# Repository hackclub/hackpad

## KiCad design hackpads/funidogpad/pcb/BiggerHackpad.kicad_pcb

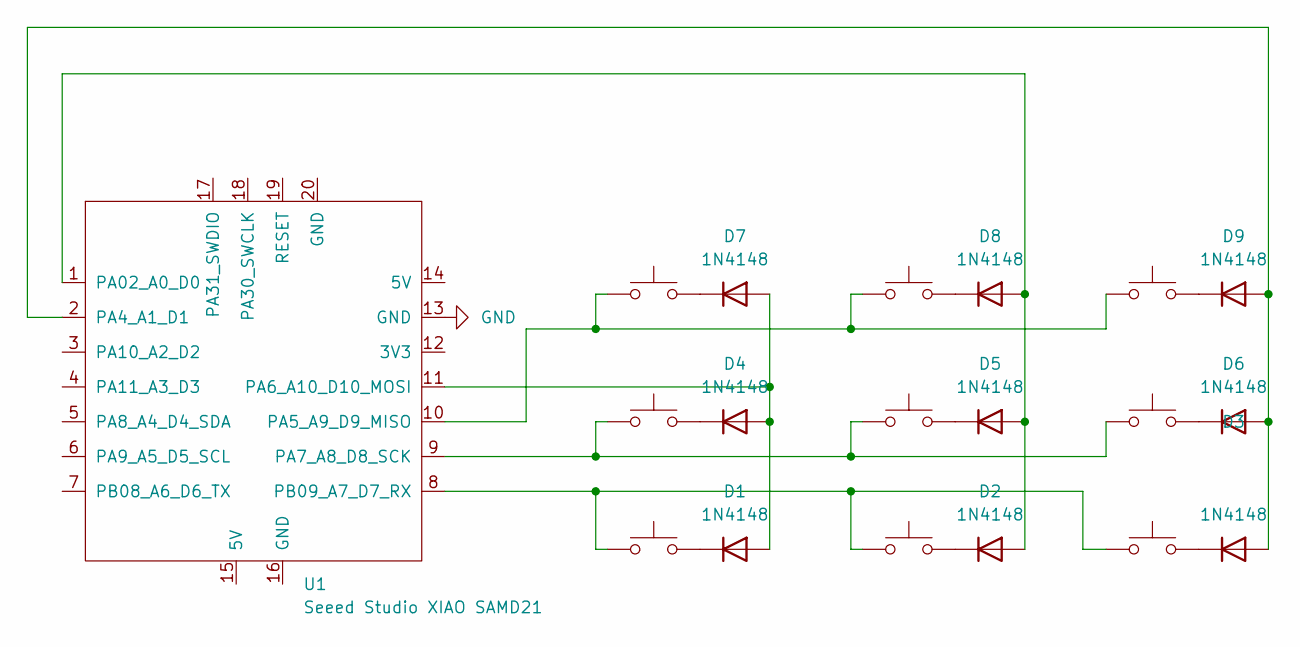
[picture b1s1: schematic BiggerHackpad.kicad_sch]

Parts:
D1, D2, D3, D4, D5, D6, D7, D8, D9: 1N4148; D_DO-35_SOD27_P7.62mm_Horizontal
SW1, SW2, SW3, SW4, SW5, SW6, SW7, SW8, SW9: SW_Push; SW_Cherry_MX_1.00u_PCB
U1: Seeed Studio XIAO SAMD21; XIAO-SAMD21-RP2040-14P-2.54-21X17.8MM (Seeeduino XIAO)

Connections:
GND: U1.13 (GND)
unnamed: D1.2 (A), D4.2 (A), D7.2 (A), U1.11 (PA6_A10_D10_MOSI)
unnamed: D1.1 (K), SW1.2
unnamed: D2.2 (A), D5.2 (A), D8.2 (A), U1.1 (PA02_A0_D0)
unnamed: D2.1 (K), SW2.2
unnamed: D3.2 (A), D6.2 (A), D9.2 (A), U1.2 (PA4_A1_D1)
unnamed: D3.1 (K), SW3.2
unnamed: D4.1 (K), SW4.2
unnamed: D5.1 (K), SW5.2
unnamed: D6.1 (K), SW6.2
unnamed: D7.1 (K), SW7.2
unnamed: D8.1 (K), SW8.2
unnamed: D9.1 (K), SW9.2
unnamed: SW7.1, SW8.1, SW9.1, U1.10 (PA5_A9_D9_MISO)
unnamed: SW4.1, SW5.1, SW6.1, U1.9 (PA7_A8_D8_SCK)
unnamed: SW1.1, SW2.1, SW3.1, U1.8 (PB09_A7_D7_RX)

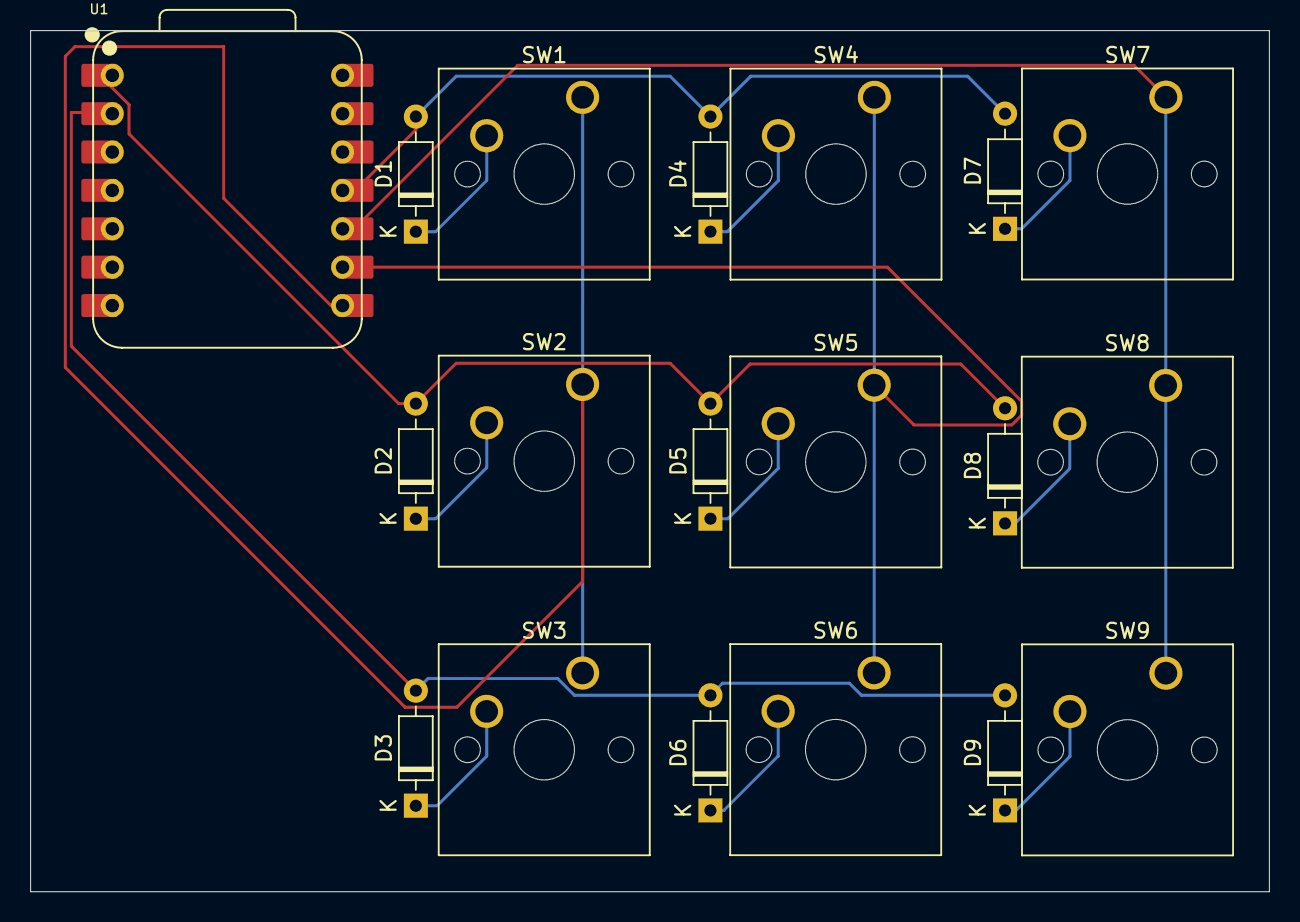
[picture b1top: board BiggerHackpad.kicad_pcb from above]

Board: 2 copper layers, 82.0 x 57.0 mm, 19 parts (0 on the bottom side), 15 nets.

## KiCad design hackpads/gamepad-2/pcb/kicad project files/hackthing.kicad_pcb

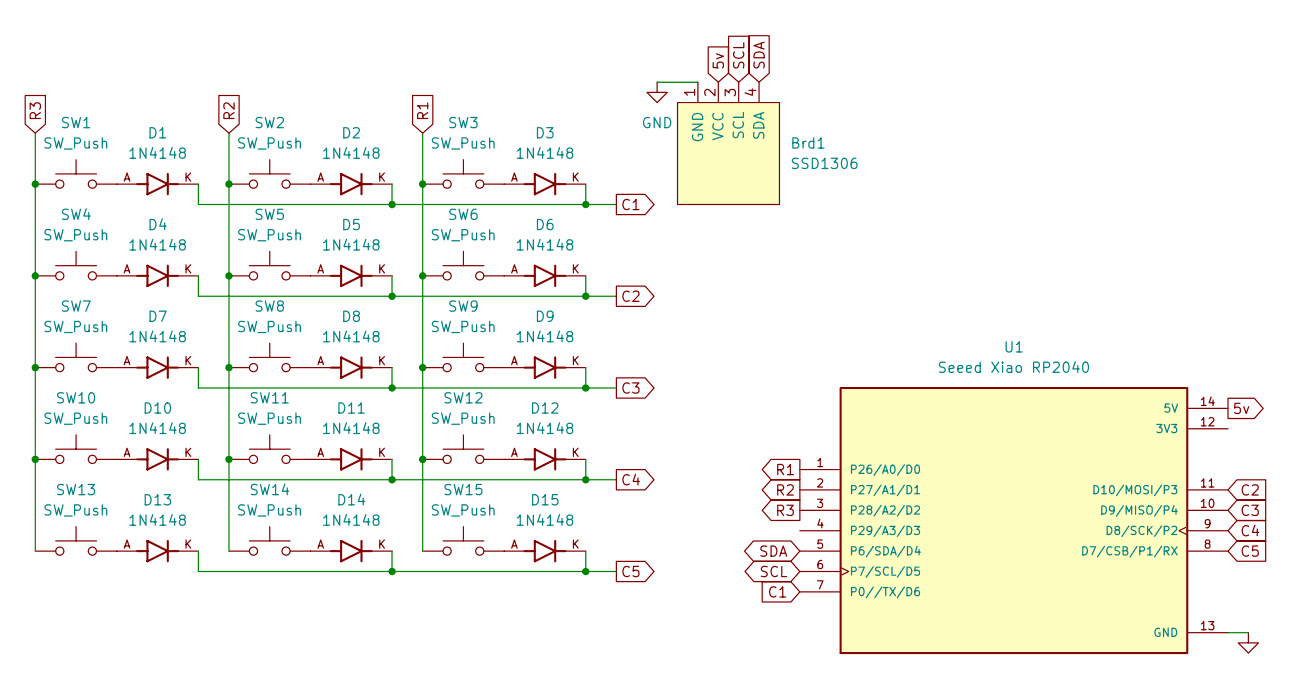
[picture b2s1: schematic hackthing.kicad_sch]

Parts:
Brd1: SSD1306; 128x64OLED
D1, D2, D3, D4, D5, D6, D7, D8, D9, D10, D11, D12, D13, D14, D15: 1N4148; DIOAD753W49L380D172B; PARTREV 5
SW1, SW2, SW3, SW4, SW5, SW6, SW7, SW8, SW9, SW10, SW11, SW12, SW13, SW14, SW15: SW_Push; MX-Solderable-1U
U1: Seeed Xiao RP2040; XIAO-Generic-Thruhole-14P-2.54-21X17.8MM; PARTREV 1.3

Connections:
5v: Brd1.2 (VCC), U1.14 (5V)
C1: D1.K, D2.K, D3.K, U1.7 (P0//TX/D6)
C2: D4.K, D5.K, D6.K, U1.11 (D10/MOSI/P3)
C3: D7.K, D8.K, D9.K, U1.10 (D9/MISO/P4)
C4: D10.K, D11.K, D12.K, U1.9 (D8/SCK/P2)
C5: D13.K, D14.K, D15.K, U1.8 (D7/CSB/P1/RX)
GND: Brd1.1 (GND), U1.13 (GND)
unnamed: D1.A, SW1.2
unnamed: D2.A, SW2.2
unnamed: D3.A, SW3.2
unnamed: D4.A, SW4.2
unnamed: D5.A, SW5.2
unnamed: D6.A, SW6.2
unnamed: D7.A, SW7.2
unnamed: D8.A, SW8.2
unnamed: D9.A, SW9.2
unnamed: D10.A, SW10.2
unnamed: D11.A, SW11.2
unnamed: D12.A, SW12.2
unnamed: D13.A, SW13.2
unnamed: D14.A, SW14.2
unnamed: D15.A, SW15.2
R1: SW3.1, SW6.1, SW9.1, SW12.1, SW15.1, U1.1 (P26/A0/D0)
R2: SW2.1, SW5.1, SW8.1, SW11.1, SW14.1, U1.2 (P27/A1/D1)
R3: SW1.1, SW4.1, SW7.1, SW10.1, SW13.1, U1.3 (P28/A2/D2)
SCL: Brd1.3 (SCL), U1.6 (P7/SCL/D5)
SDA: Brd1.4 (SDA), U1.5 (P6/SDA/D4)

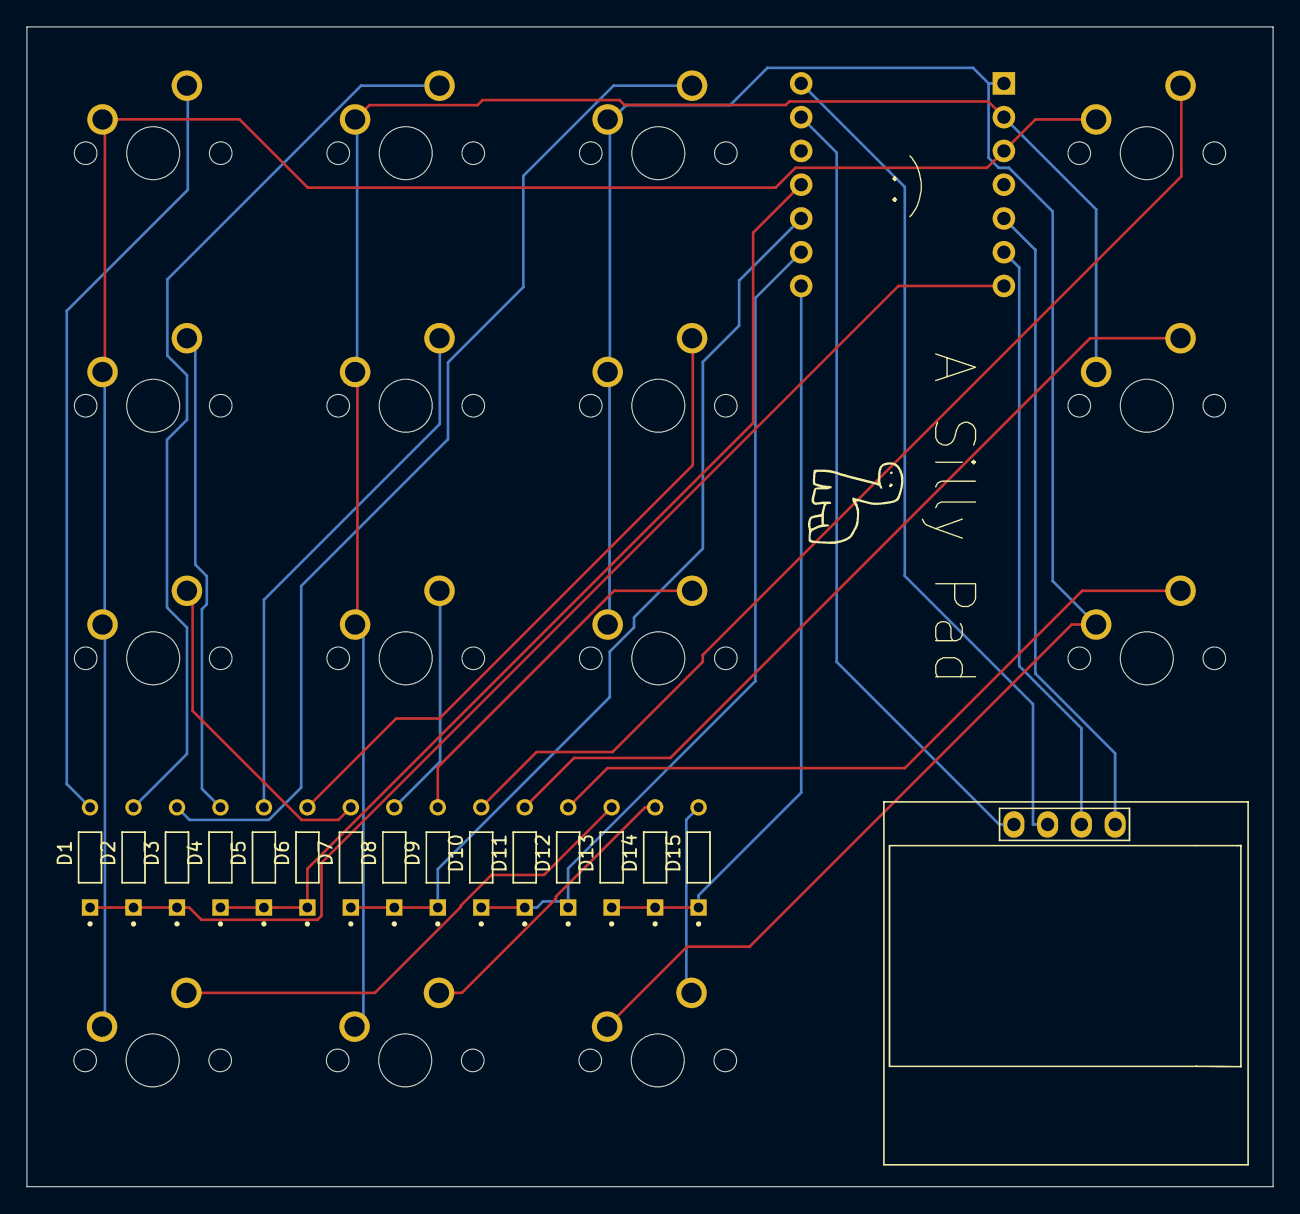
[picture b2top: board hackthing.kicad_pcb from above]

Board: 2 copper layers, 93.8 x 87.2 mm, 33 parts (1 on the bottom side), 27 nets.

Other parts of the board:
dino: LOGO

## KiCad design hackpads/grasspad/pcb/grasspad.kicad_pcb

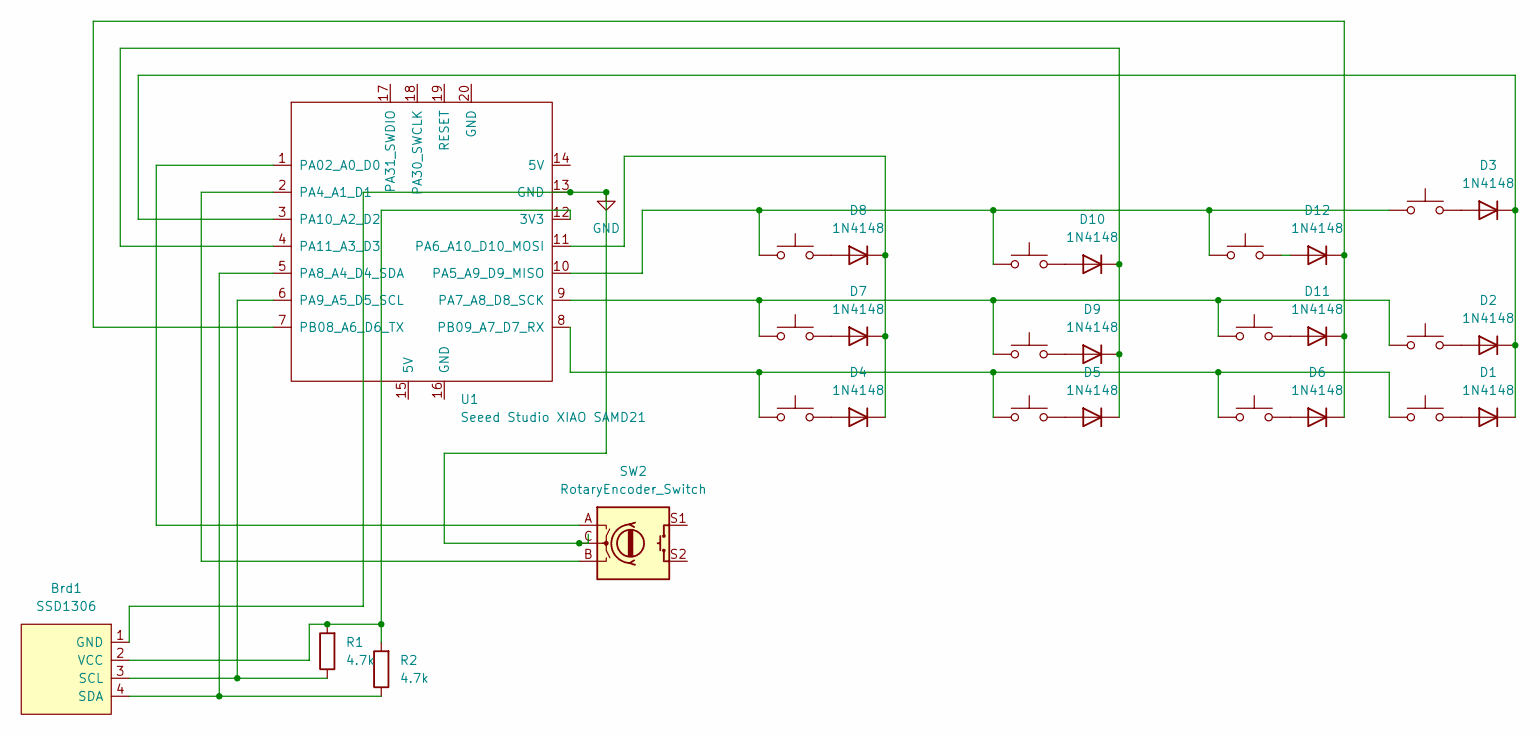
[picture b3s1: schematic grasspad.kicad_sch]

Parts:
Brd1: SSD1306; Adafruit_SSD1306
D1, D2, D3, D4, D5, D6, D7, D8, D9, D10, D11, D12: 1N4148; D_DO-35_SOD27_P7.62mm_Horizontal
R1, R2: 4.7k
SW1, SW3, SW4, SW5, SW6, SW7, SW8, SW9, SW10, SW11, SW12, SW13: SW_Push; SW_Cherry_MX_1.00u_PCB
SW2: RotaryEncoder_Switch; RotaryEncoder_Alps_EC11E-Switch_Vertical_H20mm
U1: Seeed Studio XIAO SAMD21; XIAO-Generic-Thruhole-14P-2.54-21X17.8MM

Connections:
GND: Brd1.1 (GND), SW2.C, U1.13 (GND)
unnamed: Brd1.3 (SCL), R1.1, U1.6 (PA9_A5_D5_SCL)
unnamed: Brd1.4 (SDA), R2.1, U1.5 (PA8_A4_D4_SDA)
unnamed: Brd1.2 (VCC), R1.2, R2.2, U1.12 (3V3)
unnamed: D1.2 (A), SW5.2
unnamed: D1.1 (K), D2.1 (K), D3.1 (K), U1.3 (PA10_A2_D2)
unnamed: D2.2 (A), SW1.2
unnamed: D3.2 (A), SW3.2
unnamed: D4.2 (A), SW4.2
unnamed: D4.1 (K), D7.1 (K), D8.1 (K), U1.11 (PA6_A10_D10_MOSI)
unnamed: D5.2 (A), SW6.2
unnamed: D6.2 (A), SW7.2
unnamed: D7.2 (A), SW8.2
unnamed: D8.2 (A), SW9.2
unnamed: D9.2 (A), SW10.2
unnamed: D10.2 (A), SW11.2
unnamed: D5.1 (K), D9.1 (K), D10.1 (K), U1.4 (PA11_A3_D3)
unnamed: D11.2 (A), SW12.2
unnamed: D6.1 (K), D11.1 (K), D12.1 (K), U1.7 (PB08_A6_D6_TX)
unnamed: D12.2 (A), SW13.2
unnamed: SW2.A, U1.1 (PA02_A0_D0)
unnamed: SW2.B, U1.2 (PA4_A1_D1)
unnamed: SW3.1, SW9.1, SW11.1, SW13.1, U1.10 (PA5_A9_D9_MISO)
unnamed: SW1.1, SW8.1, SW10.1, SW12.1, U1.9 (PA7_A8_D8_SCK)
unnamed: SW4.1, SW5.1, SW6.1, SW7.1, U1.8 (PB09_A7_D7_RX)

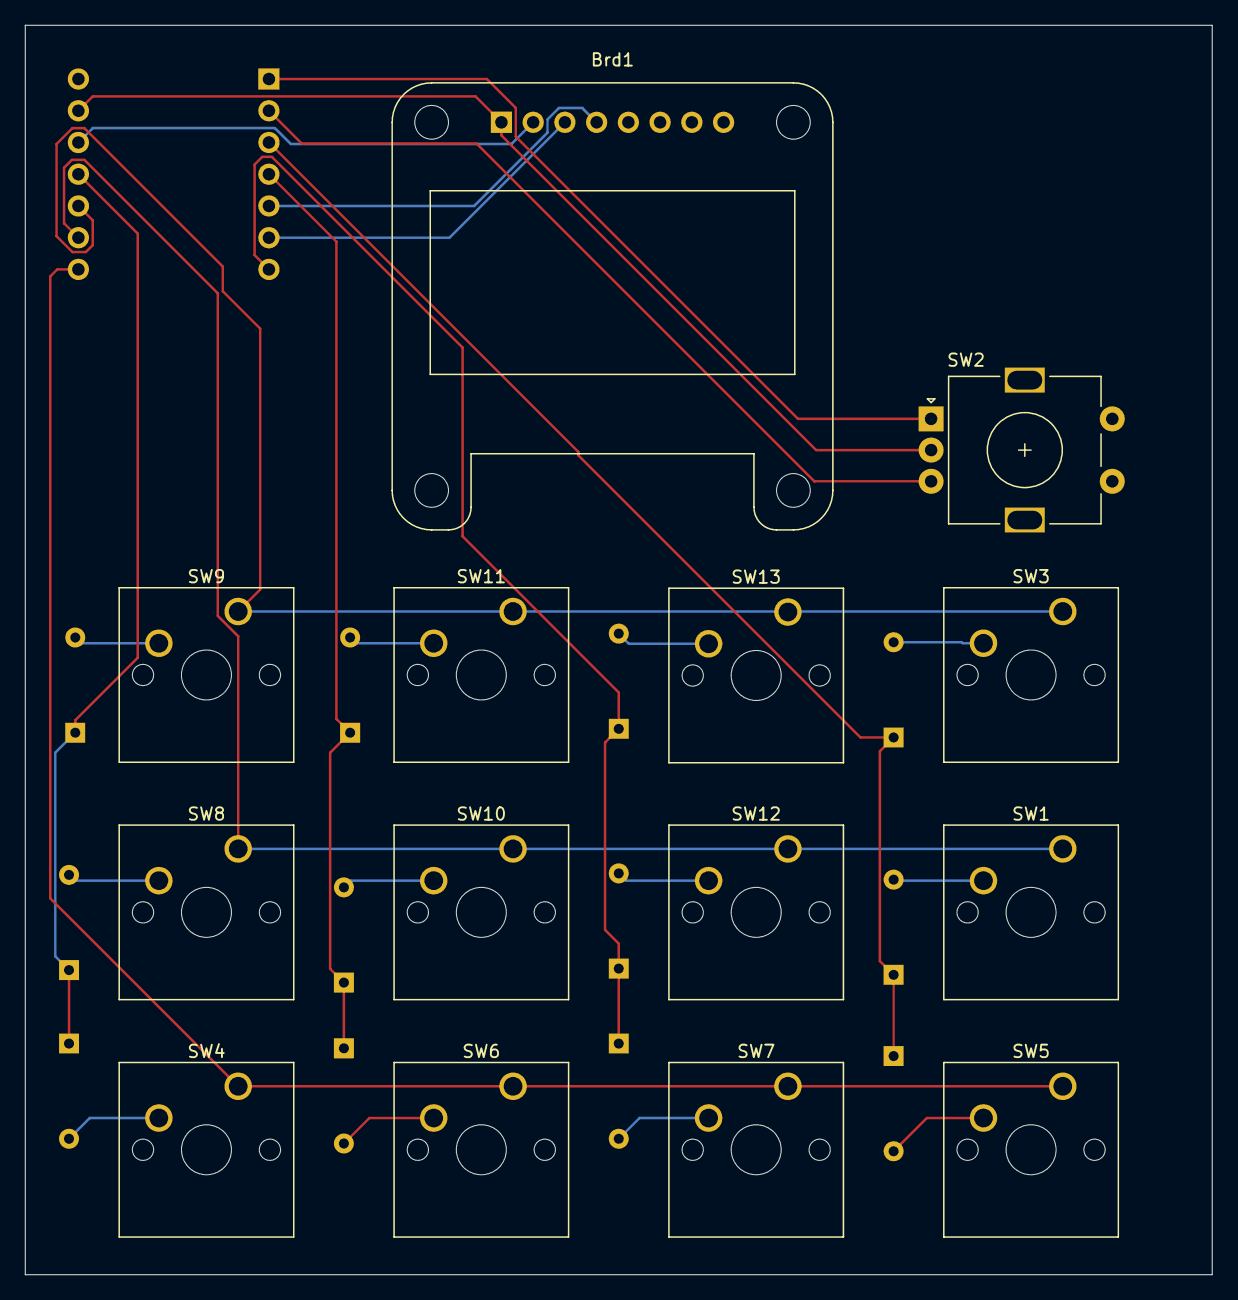
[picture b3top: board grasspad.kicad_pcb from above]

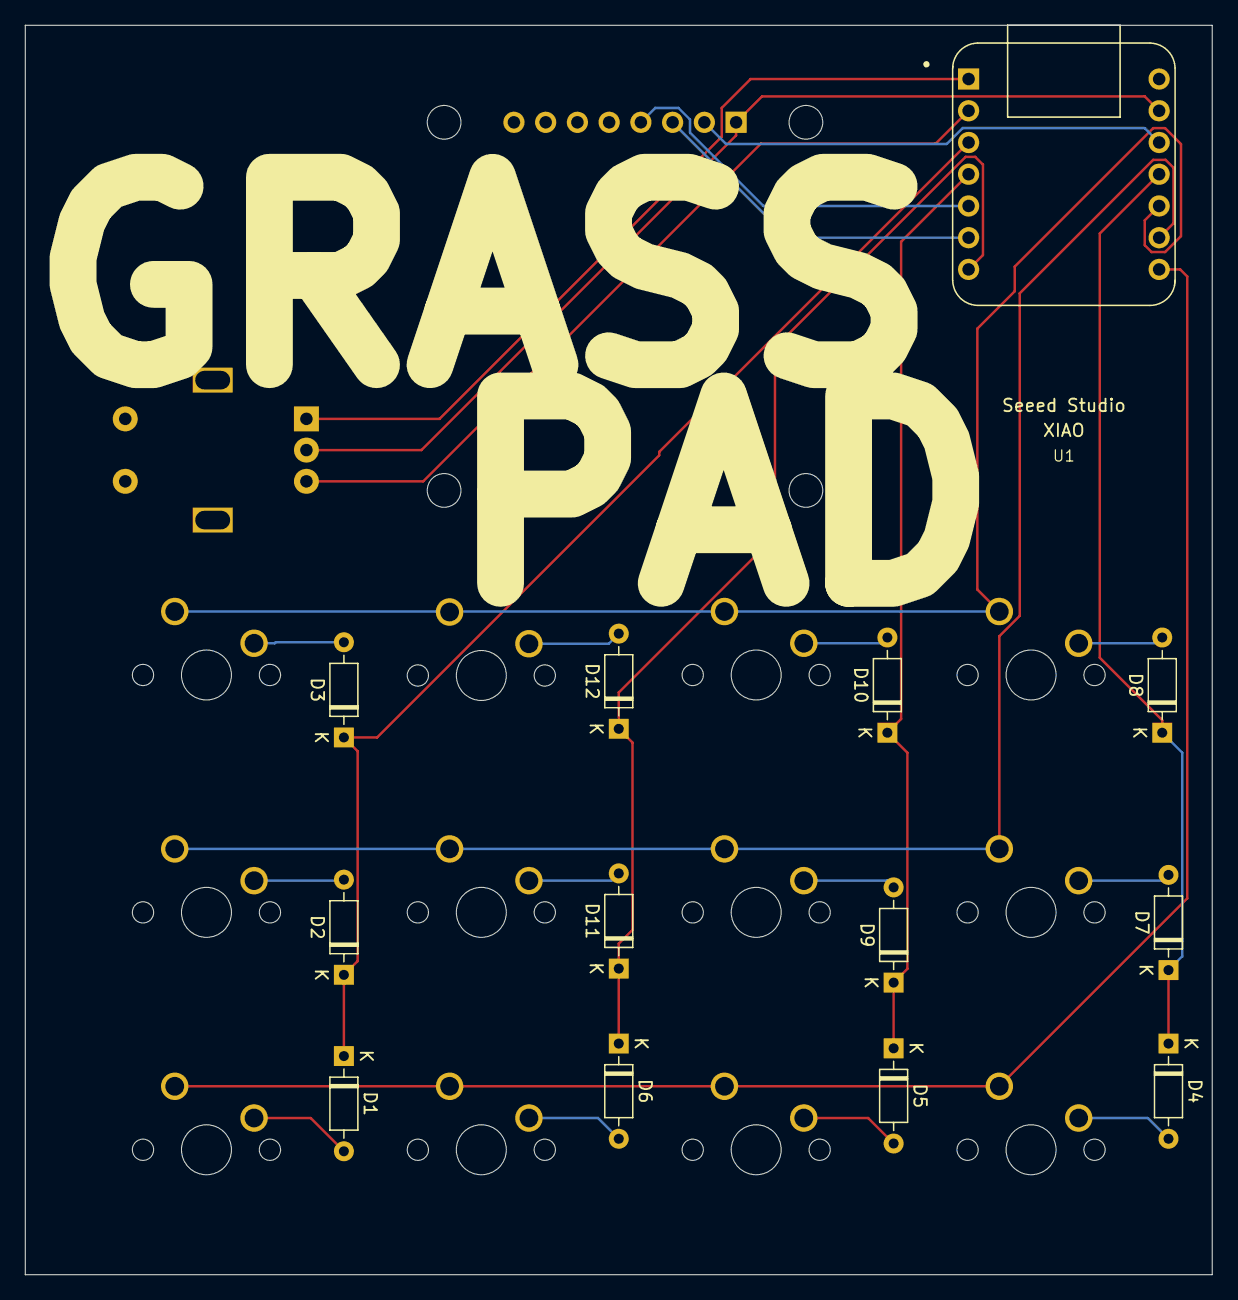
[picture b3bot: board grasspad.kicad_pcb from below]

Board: 2 copper layers, 95.0 x 100.0 mm, 27 parts (13 on the bottom side), 25 nets.

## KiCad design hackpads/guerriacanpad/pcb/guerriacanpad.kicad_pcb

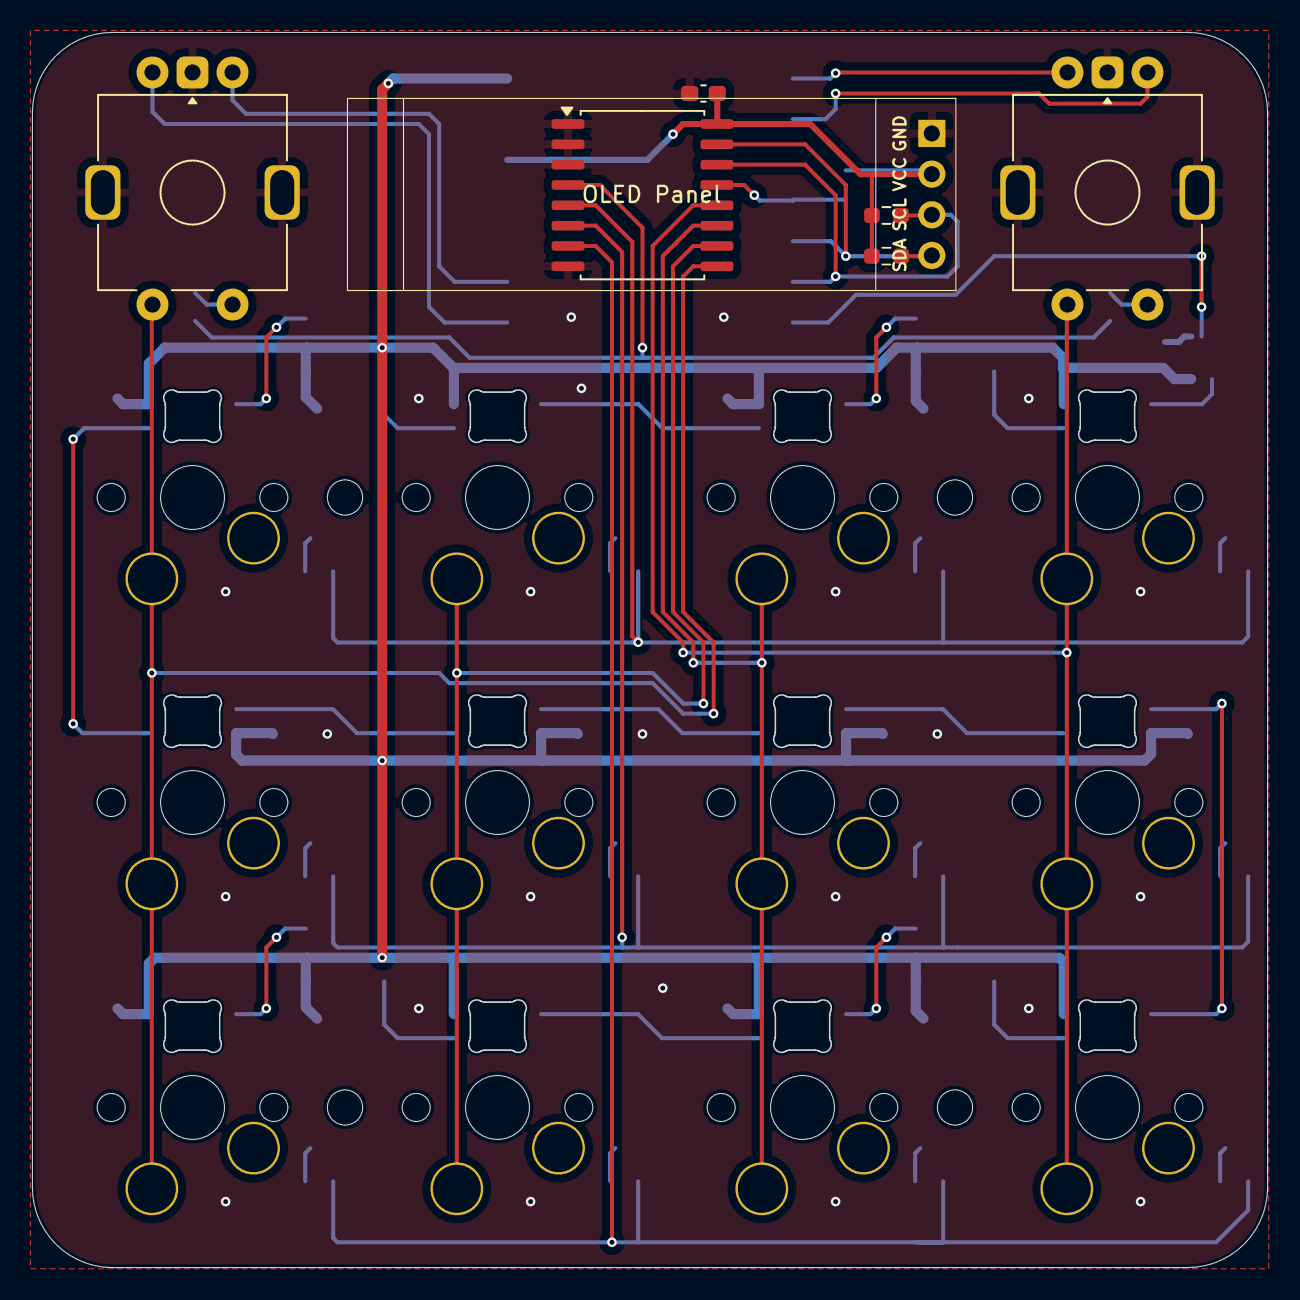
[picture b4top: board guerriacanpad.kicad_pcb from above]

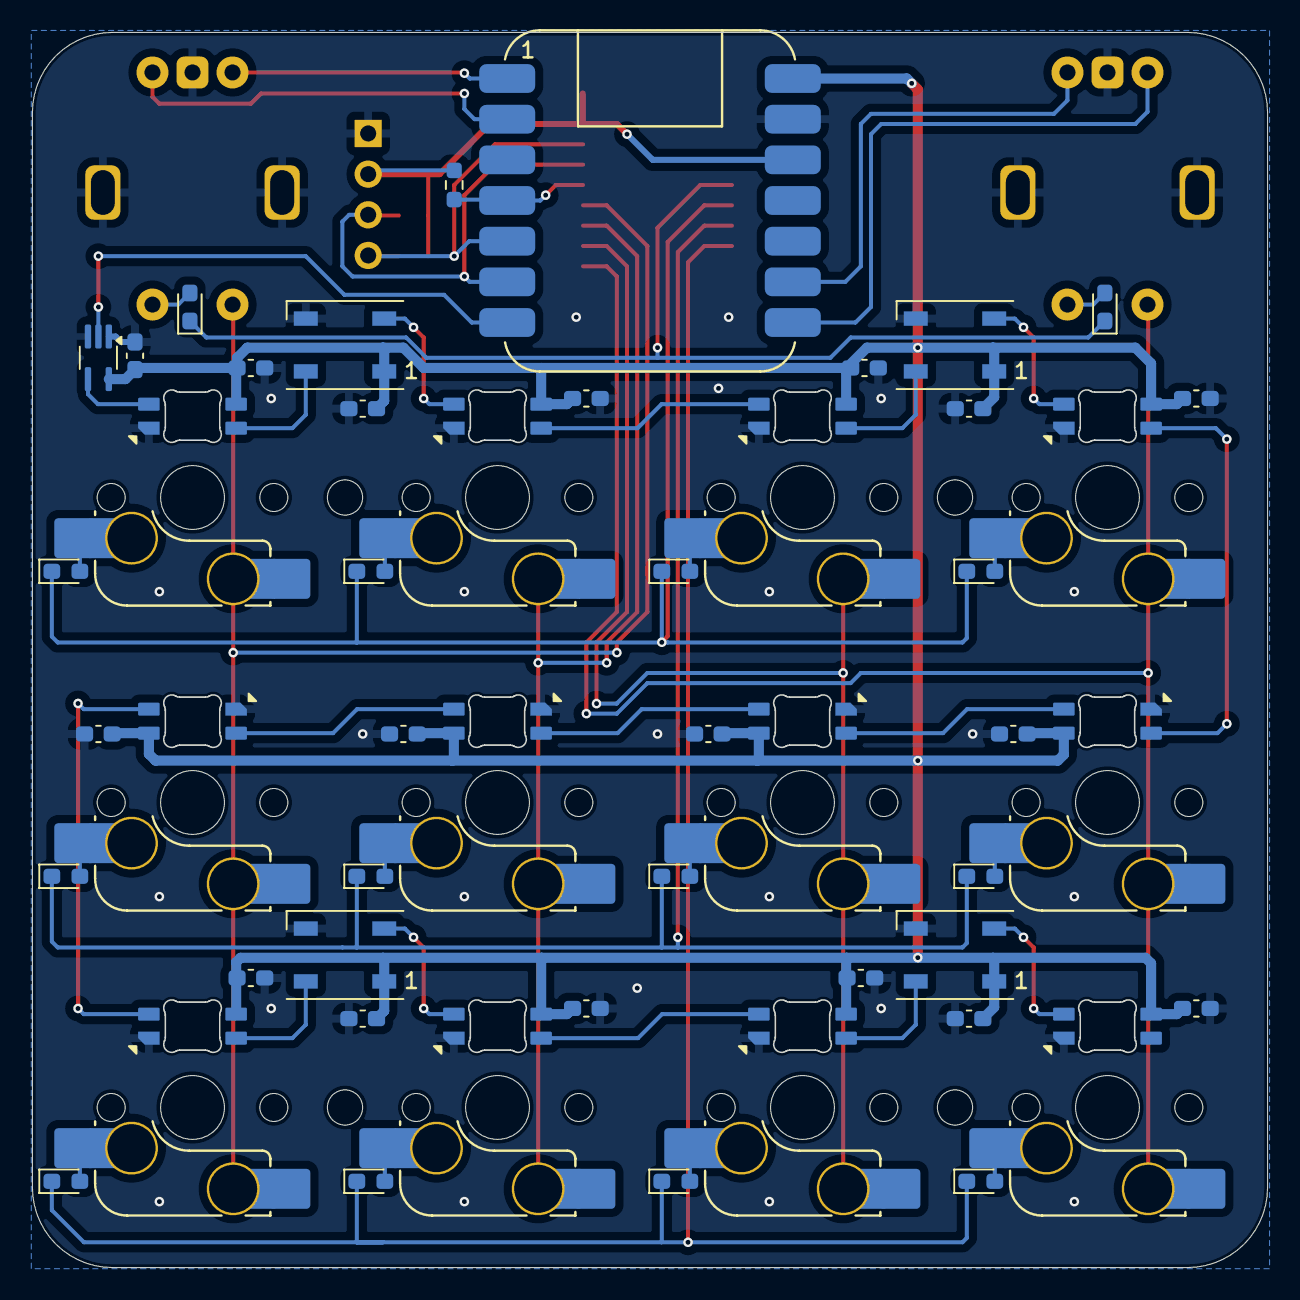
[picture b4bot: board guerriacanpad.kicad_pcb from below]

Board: 2 copper layers, 77.2 x 77.2 mm, 73 parts (62 on the bottom side), 49 nets.

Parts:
C1, C2, C3, C4, C5, C6, C7, C8, C9, C10, C11, C12, C13, C14, C15, C16, C17, C18: 100nF; C_0603_1608Metric_Pad1.08x0.95mm_HandSolder
D1, D2, D3, D4, D5, D6, D7, D8, D9, D10, D11, D12, D13, D14: D_Small; D_0603_1608Metric_Pad1.05x0.95mm_HandSolder
DS1: SSD1306_OLED_I2C; SSD1306-0.91-OLED-4pin-128x32
H1, H2, H3, H4: MountingHole; MountingHole_2.2mm_M2
LED1, LED2, LED3, LED4, LED9, LED10, LED11, LED12: SK6812MINI-E; LED_MX_6028R-ROT
LED5, LED6, LED7, LED8: SK6812MINI-E; LED_MX_6028R
LED13, LED14, LED15, LED16: WS2812B; LED_WS2812B_PLCC4_5.0x5.0mm_P3.2mm
MX1, MX2, MX3, MX4, MX5, MX6, MX7, MX8, MX9, MX10, MX11, MX12: MX_SW_HS; SW_MX_HS_CPG151101S11_1u
R1, R2: 4k7; R_0603_1608Metric_Pad0.98x0.95mm_HandSolder
R3: 10k; R_0603_1608Metric_Pad0.98x0.95mm_HandSolder
SW1, SW2: RotaryEncoder_Switch_MP; ROT_Alps_EC11E-Switch
U1: Seeeduino Xiao rp2040; Xiao_rp2040_AC_Reflow
U2: PCF8574; SOIC-16W_7.5x10.3mm_P1.27mm
U3: 74AHC1G125; SOT-353_SC-70-5_Handsoldering

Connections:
+3.3V: C17.2, DS1.2 (VCC), R1.2, R2.1, R3.1, U1.10 (3V3), U2.16 (VDD)
+5V: C1.1, C2.1, C3.1, C4.1, C5.1, C6.1, C7.1, C8.1, C9.1, C10.1, C11.1, C12.1, C13.1, C14.1, C15.1, C16.1, C18.2, LED1.1 (VDD), LED2.1 (VDD), LED3.1 (VDD), LED4.1 (VDD), LED5.1 (VDD), LED6.1 (VDD), LED7.1 (VDD), LED8.1 (VDD), LED9.1 (VDD), LED10.1 (VDD), LED11.1 (VDD), LED12.1 (VDD), LED13.1 (VDD), LED14.1 (VDD), LED15.1 (VDD), LED16.1 (VDD), U1.8 (5V), U3.5 (VCC)
COLUMN1: MX1.2, MX5.2, MX9.2, SW1.S1, U2.9 (P4)
COLUMN2: MX2.2, MX6.2, MX10.2, U2.10 (P5)
COLUMN3: MX3.2, MX7.2, MX11.2, U2.11 (P6)
COLUMN4: MX4.2, MX8.2, MX12.2, SW2.S1, U2.12 (P7)
D_LEDS_3V3: U1.7 (P0), U3.2
D_LEDS_5V: LED4.3 (DIN), U3.4
GND: C1.2, C2.2, C3.2, C4.2, C5.2, C6.2, C7.2, C8.2, C9.2, C10.2, C11.2, C12.2, C13.2, C14.2, C15.2, C16.2, C17.1, C18.1, DS1.1 (GND), LED1.4 (VSS), LED2.4 (VSS), LED3.4 (VSS), LED4.4 (VSS), LED5.4 (VSS), LED6.4 (VSS), LED7.4 (VSS), LED8.4 (VSS), LED9.4 (VSS), LED10.4 (VSS), LED11.4 (VSS), LED12.4 (VSS), LED13.3 (VSS), LED14.3 (VSS), LED15.3 (VSS), LED16.3 (VSS), SW1.C, SW1.MP, SW2.C, SW2.MP, U1.9 (GND), U2.1 (A0), U2.2 (A1), U2.3 (A2), U2.8 (VSS), U3.1, U3.3 (GND)
INT: R3.2, U1.4 (P29), U2.13 (~INT)
unnamed: D1.2 (A), MX1.1
unnamed: D2.2 (A), MX2.1
unnamed: D3.2 (A), MX3.1
unnamed: D4.2 (A), MX4.1
unnamed: D5.2 (A), MX5.1
unnamed: D6.2 (A), MX6.1
unnamed: D7.2 (A), MX7.1
unnamed: D8.2 (A), MX8.1
unnamed: D9.2 (A), MX9.1
unnamed: D10.2 (A), MX10.1
unnamed: D11.2 (A), MX11.1
unnamed: D12.2 (A), MX12.1
unnamed: D13.2 (A), SW1.S2
unnamed: D14.2 (A), SW2.S2
unnamed: LED1.3 (DIN), LED13.2 (DOUT)
unnamed: LED1.2 (DOUT), LED5.3 (DIN)
unnamed: LED2.3 (DIN), LED3.2 (DOUT)
unnamed: LED5.2 (DOUT), LED6.3 (DIN)
unnamed: LED6.2 (DOUT), LED7.3 (DIN)
unnamed: LED7.2 (DOUT), LED8.3 (DIN)
unnamed: LED10.3 (DIN), LED11.2 (DOUT)
unnamed: LED10.2 (DOUT), LED15.4 (DIN)
unnamed: LED11.3 (DIN), LED16.2 (DOUT)
unnamed: LED8.2 (DOUT), LED12.3 (DIN)
unnamed: LED12.2 (DOUT), LED16.4 (DIN)
unnamed: LED2.2 (DOUT), LED13.4 (DIN)
unnamed: LED4.2 (DOUT), LED14.4 (DIN)
unnamed: LED3.3 (DIN), LED14.2 (DOUT)
unnamed: LED9.3 (DIN), LED15.2 (DOUT)
ROT1A: SW1.A, U1.13 (P2)
ROT1B: SW1.B, U1.14 (P1)
ROT2A: SW2.A, U1.2 (P27)
ROT2B: SW2.B, U1.1 (P26)
ROW1: D13.1 (K), D14.1 (K), U2.4 (P0)
ROW2: D1.1 (K), D2.1 (K), D3.1 (K), D4.1 (K), U2.5 (P1)
ROW3: D5.1 (K), D6.1 (K), D7.1 (K), D8.1 (K), U2.6 (P2)
ROW4: D9.1 (K), D10.1 (K), D11.1 (K), D12.1 (K), U2.7 (P3)
SCL: DS1.3 (SCL), R2.2, U1.6 (P7), U2.14 (SCL)
SDA: DS1.4 (SDA), R1.1, U1.5 (P6), U2.15 (SDA)

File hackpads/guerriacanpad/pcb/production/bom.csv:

Designator,Footprint,Quantity,Value,LCSC Part #
"D1, D10, D11, D12, D17, D18, D2, D3, D4, D5, D6, D7, D8, D9",0603,14,D_Small,
"D13, D14, D15, D16",LED_WS2812B_PLCC4_5.0x5.0mm_P3.2mm,4,WS2812B,
DS1,SSD1306-0.91-OLED-4pin-128x32,1,SSD1306_OLED_I2C,
"LED1, LED10, LED11, LED12, LED2, LED3, LED4, LED9",LED_MX_6028R-ROT,8,SK6812MINI-E,
"LED5, LED6, LED7, LED8",LED_MX_6028R,4,SK6812MINI-E,
"MX1, MX10, MX11, MX12, MX2, MX3, MX4, MX5, MX6, MX7, MX8, MX9",SW_MX_HS_CPG151101S11_1u,12,MX_SW_HS,
"SW1, SW2",ROT_Alps_EC11E-Switch,2,RotaryEncoder_Switch_MP,
U2,SOIC-16W_7.5x10.3mm_P1.27mm,1,PCF8574,
U3,SOT-353_SC-70-5_Handsoldering,1,74AHC1G125,

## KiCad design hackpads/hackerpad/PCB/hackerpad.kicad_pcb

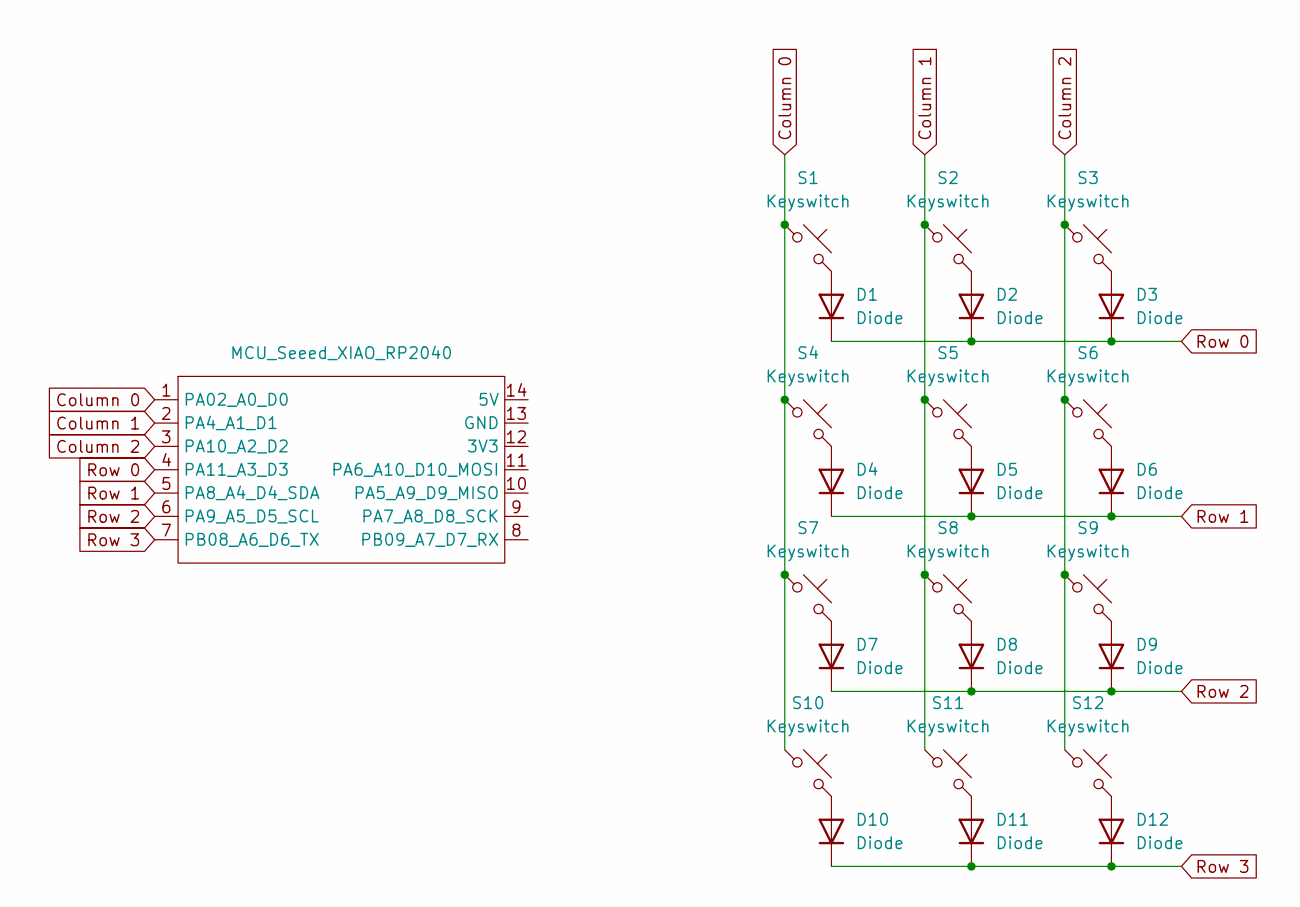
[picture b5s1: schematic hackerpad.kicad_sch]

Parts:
D1, D2, D3, D4, D5, D6, D7, D8, D9, D10, D11, D12: Diode; Diode_DO-35
S1, S2, S3, S4, S5, S6, S7, S8, S9, S10, S11, S12: Keyswitch; MX_PCB_1.00u
U1: MCU_Seeed_XIAO_RP2040; Seeed_XIAO_RP2040

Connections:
Column 0: S1.1, S4.1, S7.1, S10.1, U1.1 (PA02_A0_D0)
Column 1: S2.1, S5.1, S8.1, S11.1, U1.2 (PA4_A1_D1)
Column 2: S3.1, S6.1, S9.1, S12.1, U1.3 (PA10_A2_D2)
unnamed: D1.2 (A), S1.2
unnamed: D2.2 (A), S2.2
unnamed: D3.2 (A), S3.2
unnamed: D4.2 (A), S4.2
unnamed: D5.2 (A), S5.2
unnamed: D6.2 (A), S6.2
unnamed: D7.2 (A), S7.2
unnamed: D8.2 (A), S8.2
unnamed: D9.2 (A), S9.2
unnamed: D10.2 (A), S10.2
unnamed: D11.2 (A), S11.2
unnamed: D12.2 (A), S12.2
Row 0: D1.1 (K), D2.1 (K), D3.1 (K), U1.4 (PA11_A3_D3)
Row 1: D4.1 (K), D5.1 (K), D6.1 (K), U1.5 (PA8_A4_D4_SDA)
Row 2: D7.1 (K), D8.1 (K), D9.1 (K), U1.6 (PA9_A5_D5_SCL)
Row 3: D10.1 (K), D11.1 (K), D12.1 (K), U1.7 (PB08_A6_D6_TX)

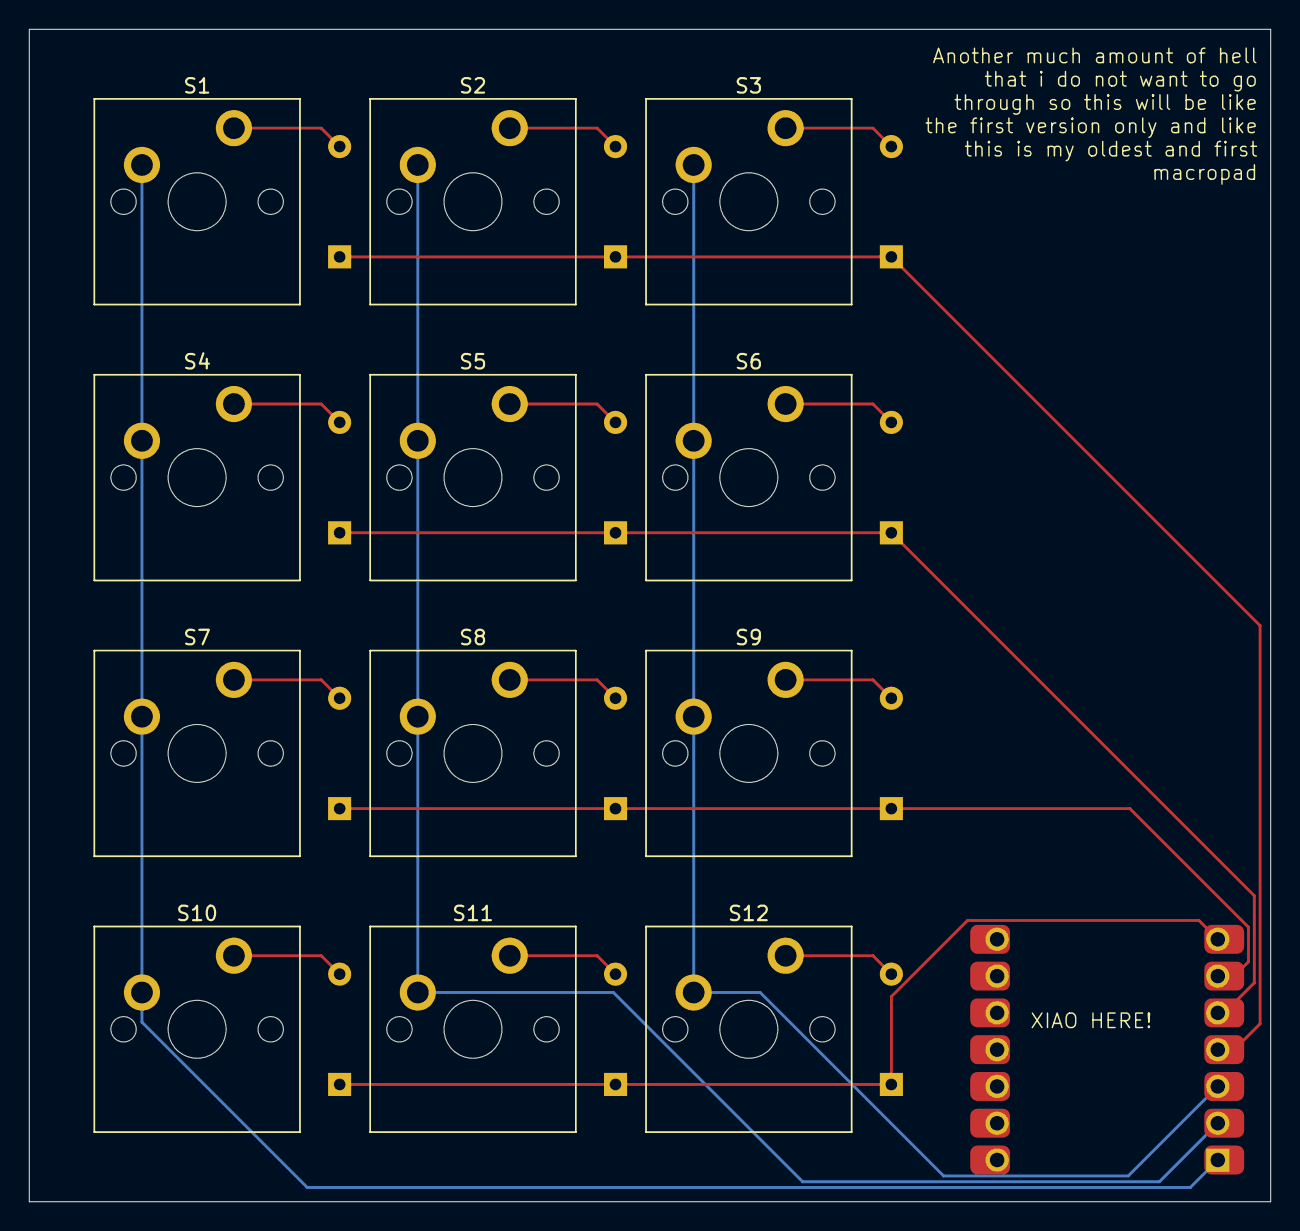
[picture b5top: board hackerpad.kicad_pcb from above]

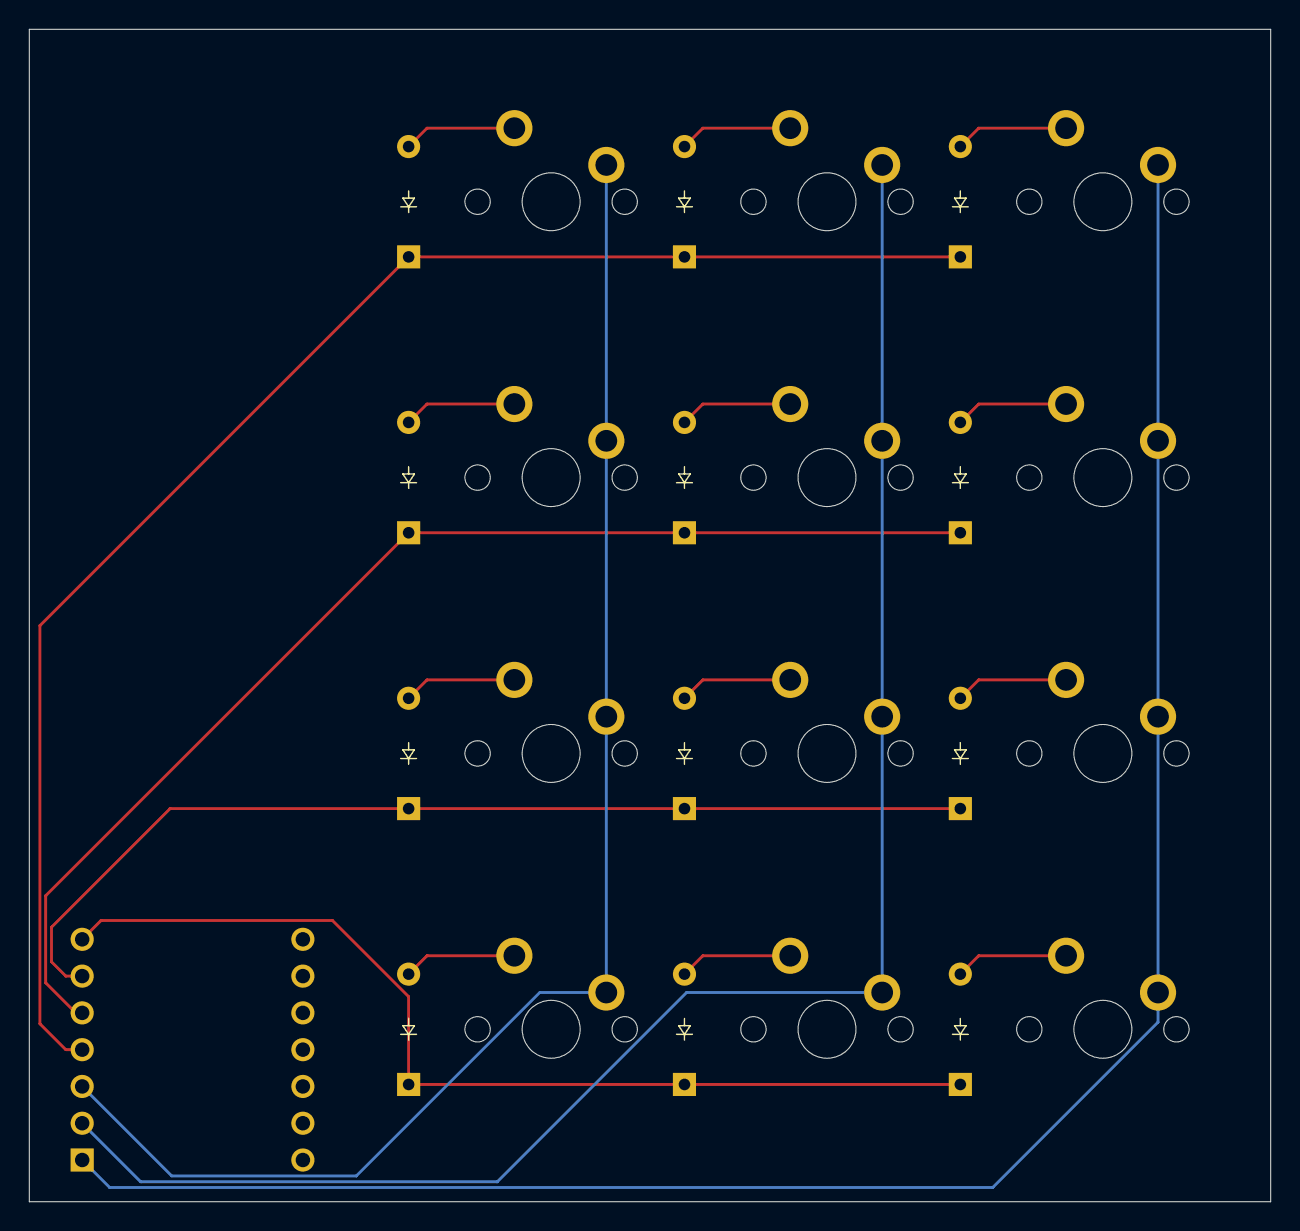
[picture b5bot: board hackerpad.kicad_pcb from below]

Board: 2 copper layers, 85.7 x 81.0 mm, 25 parts (12 on the bottom side), 19 nets.

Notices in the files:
hackpads/hackmacro/PCB/hackpad1.kicad_pcb:
Eduardo © 2024 - Inspired by Work Louder
